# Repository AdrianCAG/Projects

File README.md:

# Projects Collection

This folder contains a collection of programs and code for you to explore, learn from, and experiment with. If you're curious and want to learn, feel free to dive in and use anything in this folder.

## License

All contents in this folder are provided under the MIT License. You are free to use, copy, modify, and distribute the code as long as you include the original copyright and license notice.

See the [MIT License](LICENSE) file for full details.

---

Happy learning and coding!

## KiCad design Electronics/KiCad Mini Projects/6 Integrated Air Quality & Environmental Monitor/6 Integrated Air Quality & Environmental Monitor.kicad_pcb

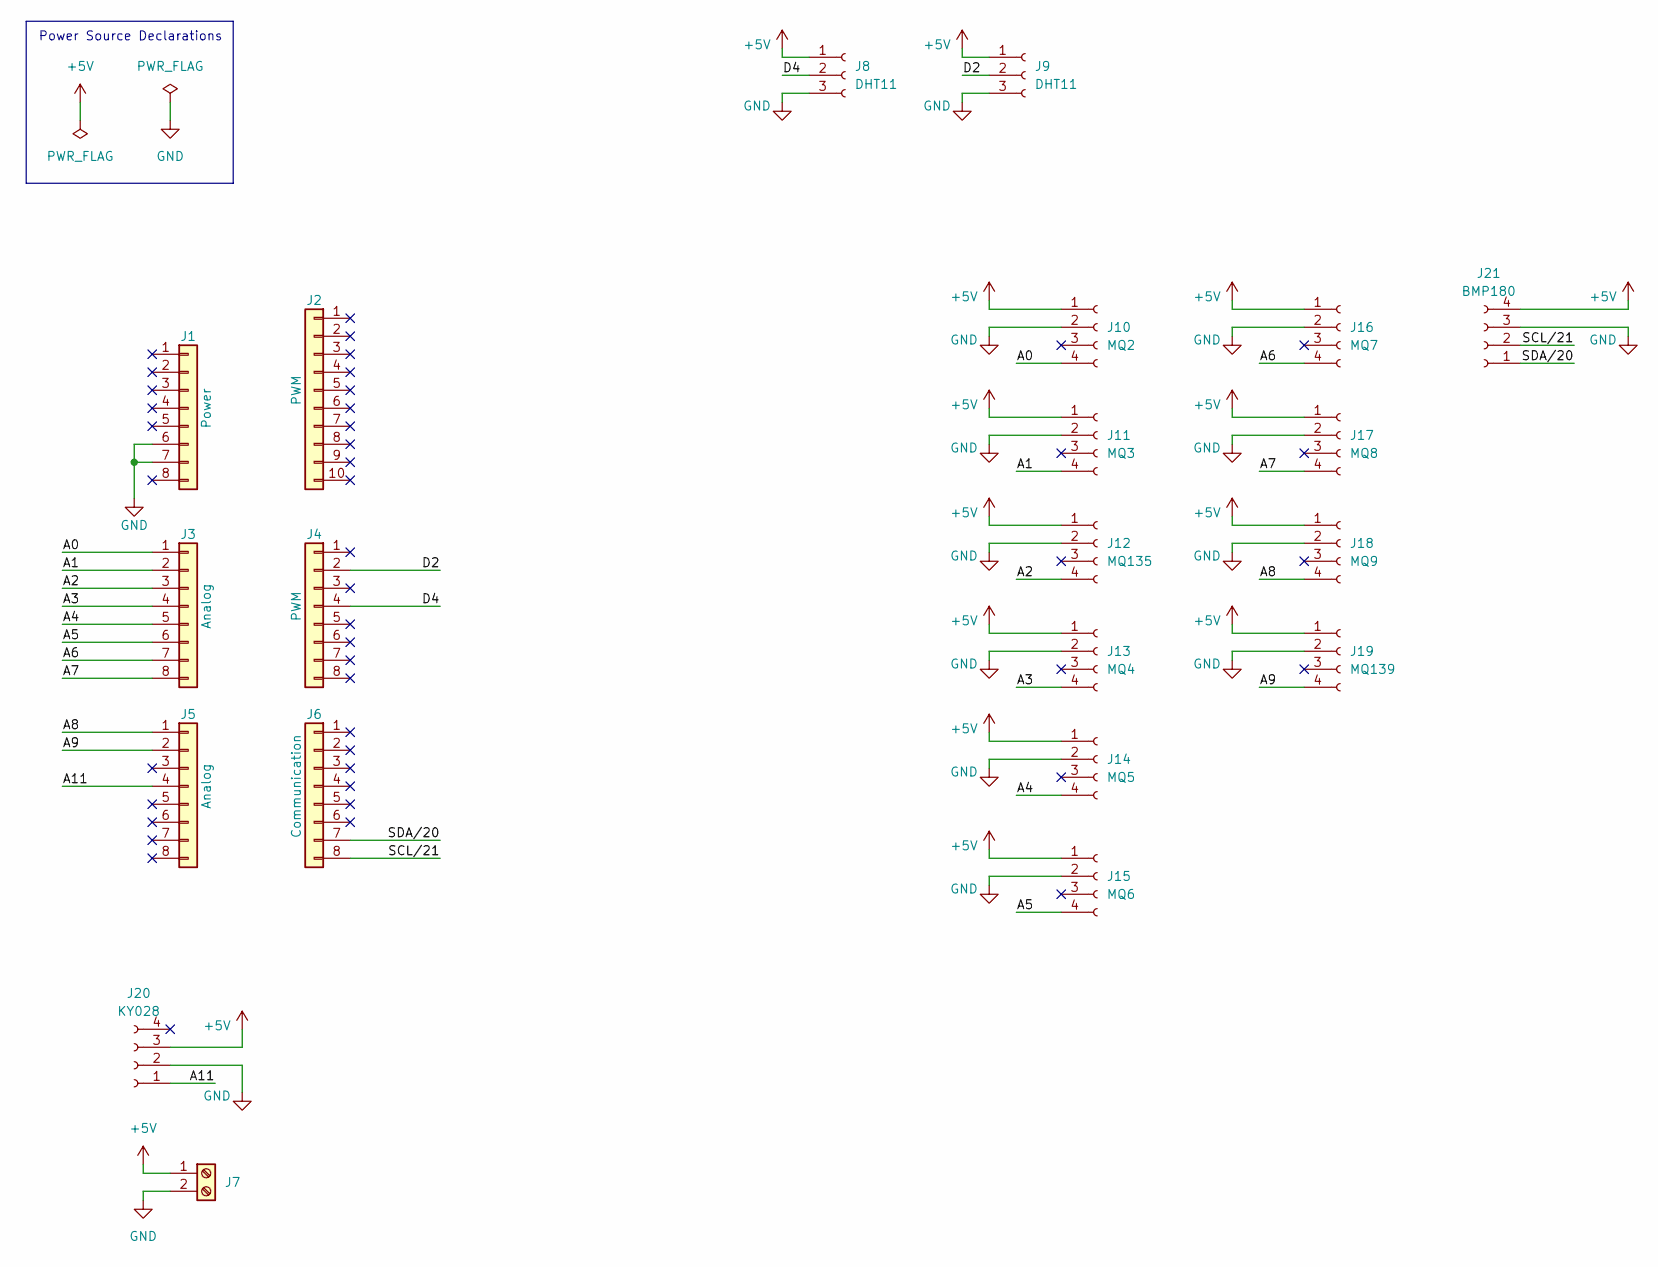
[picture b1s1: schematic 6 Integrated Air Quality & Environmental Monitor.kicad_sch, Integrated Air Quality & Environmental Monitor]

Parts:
J1: Power; PinSocket_1x08_P2.54mm_Vertical
J2: PWM; PinSocket_1x10_P2.54mm_Vertical
J3, J5: Analog; PinSocket_1x08_P2.54mm_Vertical
J4: PWM; PinSocket_1x08_P2.54mm_Vertical
J6: Communication; PinSocket_1x08_P2.54mm_Vertical
J7: Screw_Terminal_01x02; TerminalBlock_Phoenix_MKDS-1-2-3.81_1x02_P3.81mm_Horizontal
J8, J9: DHT11; PinSocket_1x03_P2.54mm_Vertical
J10: MQ2; MQ_Module_Vertical; Parts 2.54mm female header socket
J11: MQ3; MQ_Module_Vertical; Parts 2.54mm female header socket
J12: MQ135; MQ_Module_Vertical; Parts 2.54mm female header socket
J13: MQ4; PinSocket_1x04_P2.54mm_Vertical; Parts 2.54mm female header socket
J14: MQ5; PinSocket_1x04_P2.54mm_Vertical; Parts 2.54mm female header socket
J15: MQ6; MQ_Module_Vertical; Parts 2.54mm female header socket
J16: MQ7; MQ_Module_Vertical; Parts 2.54mm female header socket
J17: MQ8; MQ_Module_Vertical; Parts 2.54mm female header socket
J18: MQ9; PinSocket_1x04_P2.54mm_Vertical; Parts 2.54mm female header socket
J19: MQ139; PinHeader_1x04_P2.54mm_Vertical; Parts 2.54mm female header socket
J20: KY028; PinSocket_1x04_P2.54mm_Vertical; Parts 2.54mm female header socket
J21: BMP180; PinSocket_1x04_P2.54mm_Vertical; Parts 2.54mm female header socket

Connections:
+5V: J7.1, J8.1, J9.1, J10.1, J11.1, J12.1, J13.1, J14.1, J15.1, J16.1, J17.1, J18.1, J19.1, J20.3, J21.4
/A0: J3.1, J10.4
/A1: J3.2, J11.4
/A2: J3.3, J12.4
/A3: J3.4, J13.4
/A4: J3.5, J14.4
/A5: J3.6, J15.4
/A6: J3.7, J16.4
/A7: J3.8, J17.4
/A8: J5.1, J18.4
/A9: J5.2, J19.4
/A11: J5.4, J20.1
/D2: J4.2, J9.2
/D4: J4.4, J8.2
/SCL/21: J6.8, J21.2
/SDA/20: J6.7, J21.1
GND: J1.6, J1.7, J7.2, J8.3, J9.3, J10.2, J11.2, J12.2, J13.2, J14.2, J15.2, J16.2, J17.2, J18.2, J19.2, J20.2, J21.3

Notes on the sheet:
Power Source Declarations

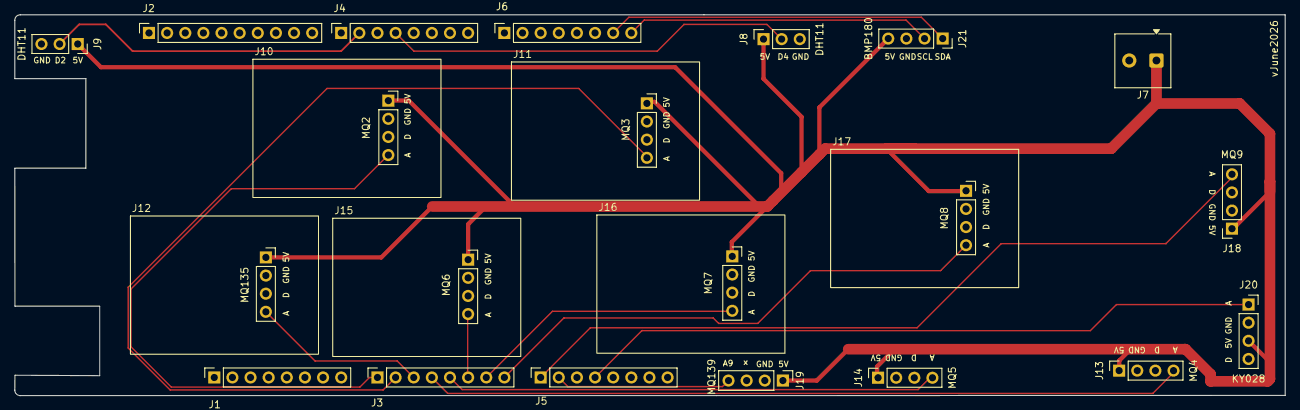
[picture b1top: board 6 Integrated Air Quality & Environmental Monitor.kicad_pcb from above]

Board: 2 copper layers, 178.0 x 53.3 mm, 21 parts (0 on the bottom side), 17 nets.

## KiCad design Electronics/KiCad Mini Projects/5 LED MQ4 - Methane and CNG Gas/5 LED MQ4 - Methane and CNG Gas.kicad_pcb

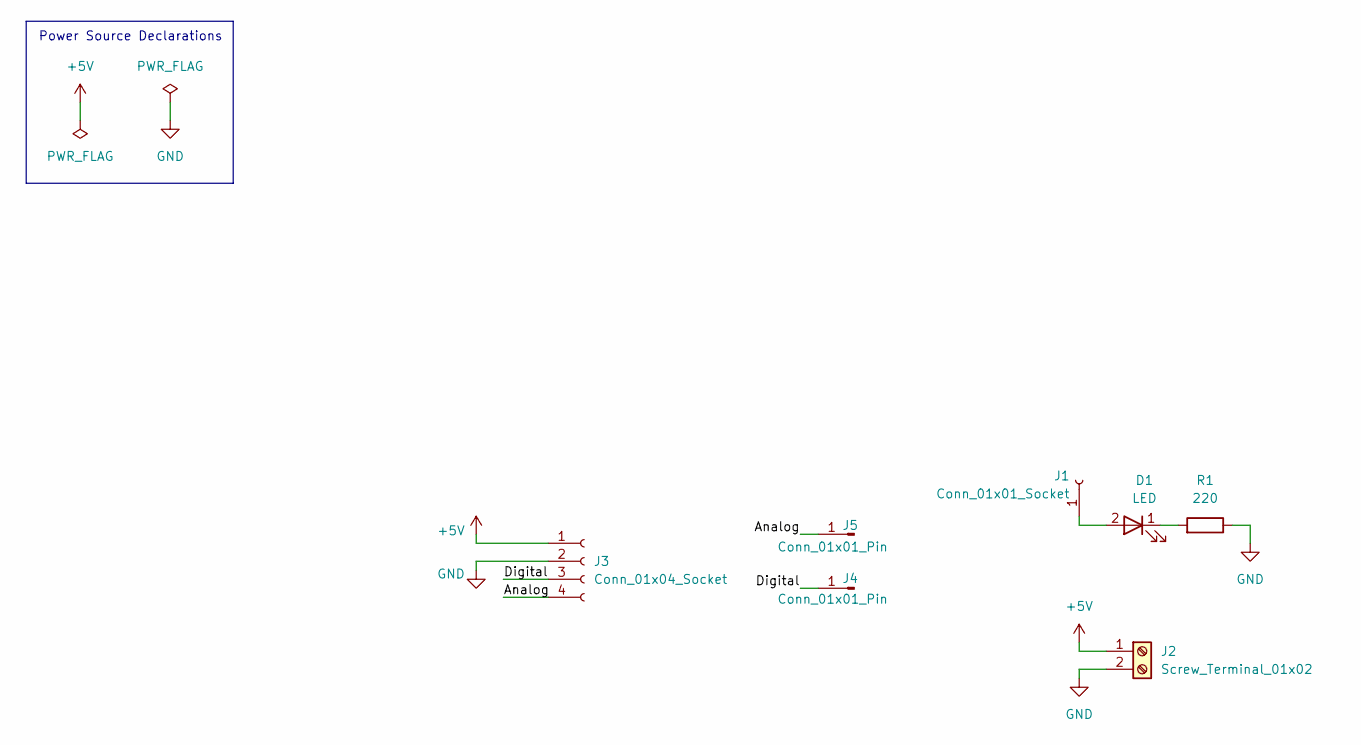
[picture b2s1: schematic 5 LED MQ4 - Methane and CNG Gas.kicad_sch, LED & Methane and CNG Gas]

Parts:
D1: LED; LED_D5.0mm; Parts 5mm LED
J1: Conn_01x01_Socket; PinSocket_1x01_P2.54mm_Vertical; Parts 2.54mm female header socket
J2: Screw_Terminal_01x02; TerminalBlock_Phoenix_MKDS-1-2-3.81_1x02_P3.81mm_Horizontal; Parts KF128 3.81mm 2P
J3: Conn_01x04_Socket; PinSocket_1x04_P2.54mm_Vertical; Parts 2.54mm female header socket
J4, J5: Conn_01x01_Pin; PinHeader_1x01_P2.54mm_Vertical; Parts 2.54mm pin header
R1: 220; R_1206_3216Metric_Pad1.30x1.75mm_HandSolder; Parts 1206 SMD resistor 220 ohm

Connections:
+5V: J2.1, J3.1
/Analog: J3.4, J5.1 (Pin_1_1)
/Digital: J3.3, J4.1 (Pin_1_1)
GND: J2.2, J3.2, R1.1
unnamed: D1.2 (A), J1.1 (Pin_1_1)
unnamed: D1.1 (K), R1.2

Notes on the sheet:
Power Source Declarations

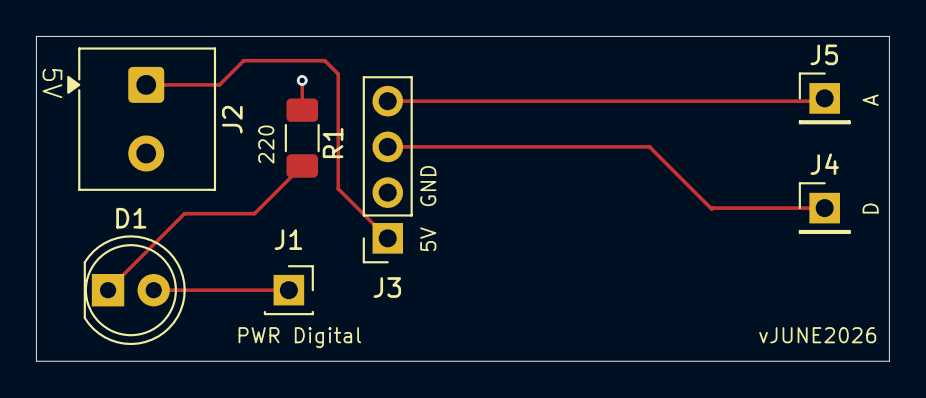
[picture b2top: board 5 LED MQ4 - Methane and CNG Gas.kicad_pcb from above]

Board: 2 copper layers, 47.4 x 18.0 mm, 7 parts (0 on the bottom side), 6 nets.

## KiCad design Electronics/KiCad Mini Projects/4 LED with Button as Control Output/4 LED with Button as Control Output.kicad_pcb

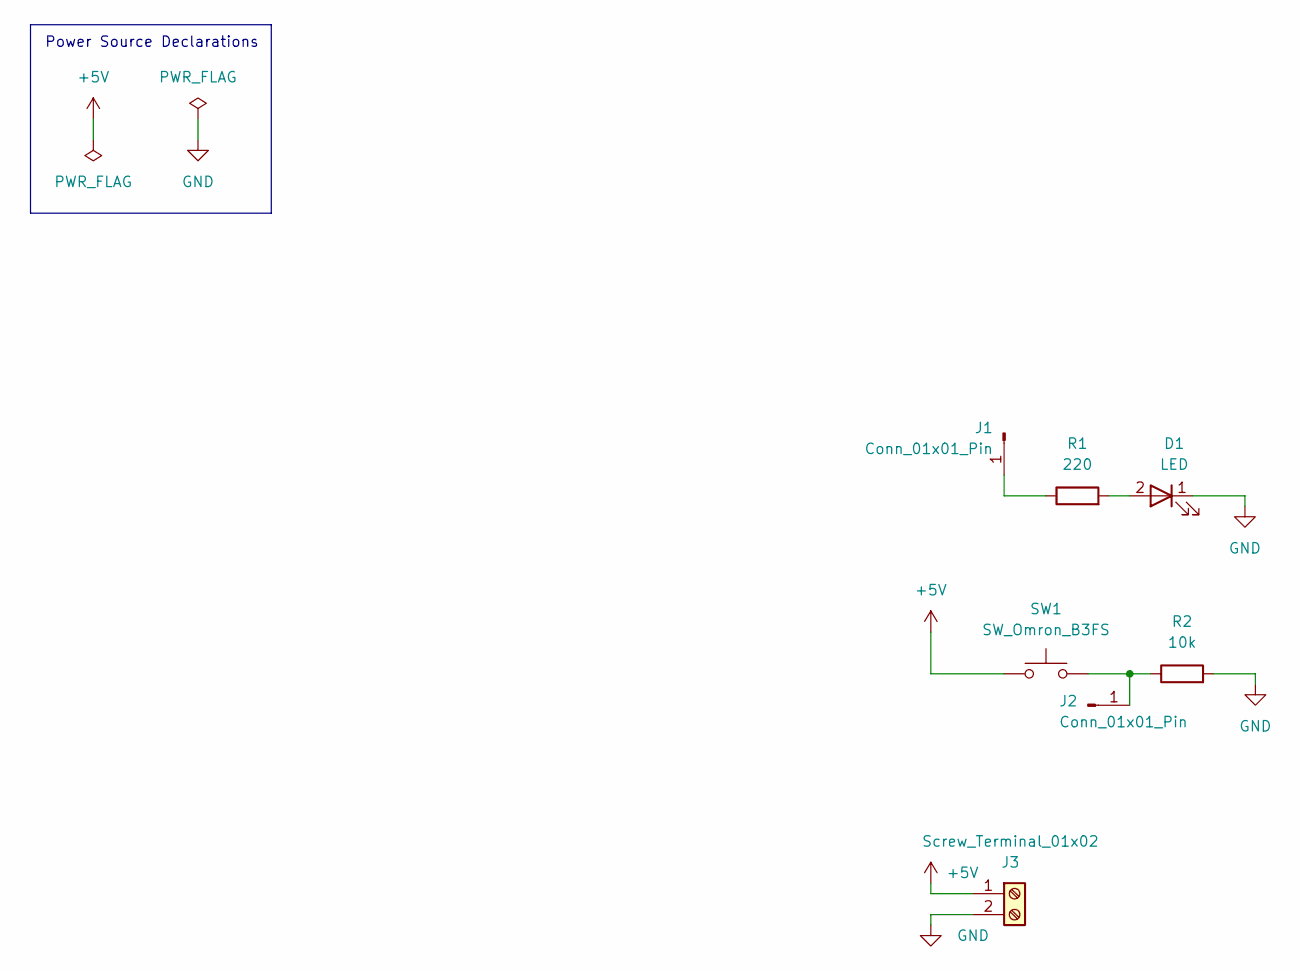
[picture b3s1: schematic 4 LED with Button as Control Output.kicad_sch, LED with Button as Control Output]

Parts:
D1: LED; LED_D5.0mm; Parts 5mm LED
J1, J2: Conn_01x01_Pin; PinHeader_1x01_P2.54mm_Vertical; Parts 2.54mm pin header
J3: Screw_Terminal_01x02; TerminalBlock_Phoenix_MKDS-1-2-3.81_1x02_P3.81mm_Horizontal; Parts KF128 3.81mm 2P
R1: 220; R_1206_3216Metric_Pad1.30x1.75mm_HandSolder; Parts 1206 SMD resistor 220 ohm
R2: 10k; R_1206_3216Metric_Pad1.30x1.75mm_HandSolder; Parts 1206 SMD resistor 10k ohm
SW1: SW_Omron_B3FS; SW_PUSH_6mm; Parts 6x6x5mm tactile switch

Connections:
+5V: J3.1, SW1.1
GND: D1.1 (K), J3.2, R2.2
unnamed: D1.2 (A), R1.2
unnamed: J1.1 (Pin_1_1), R1.1
unnamed: J2.1 (Pin_1_1), R2.1, SW1.2

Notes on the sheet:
Power Source Declarations

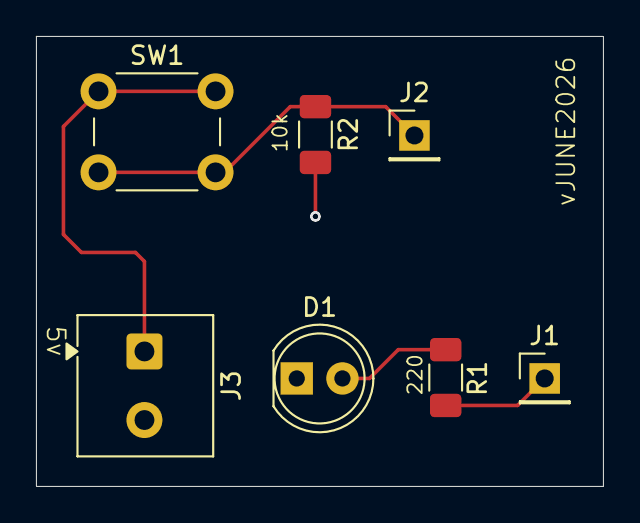
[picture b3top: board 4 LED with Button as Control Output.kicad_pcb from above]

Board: 2 copper layers, 31.5 x 25.0 mm, 7 parts (0 on the bottom side), 5 nets.

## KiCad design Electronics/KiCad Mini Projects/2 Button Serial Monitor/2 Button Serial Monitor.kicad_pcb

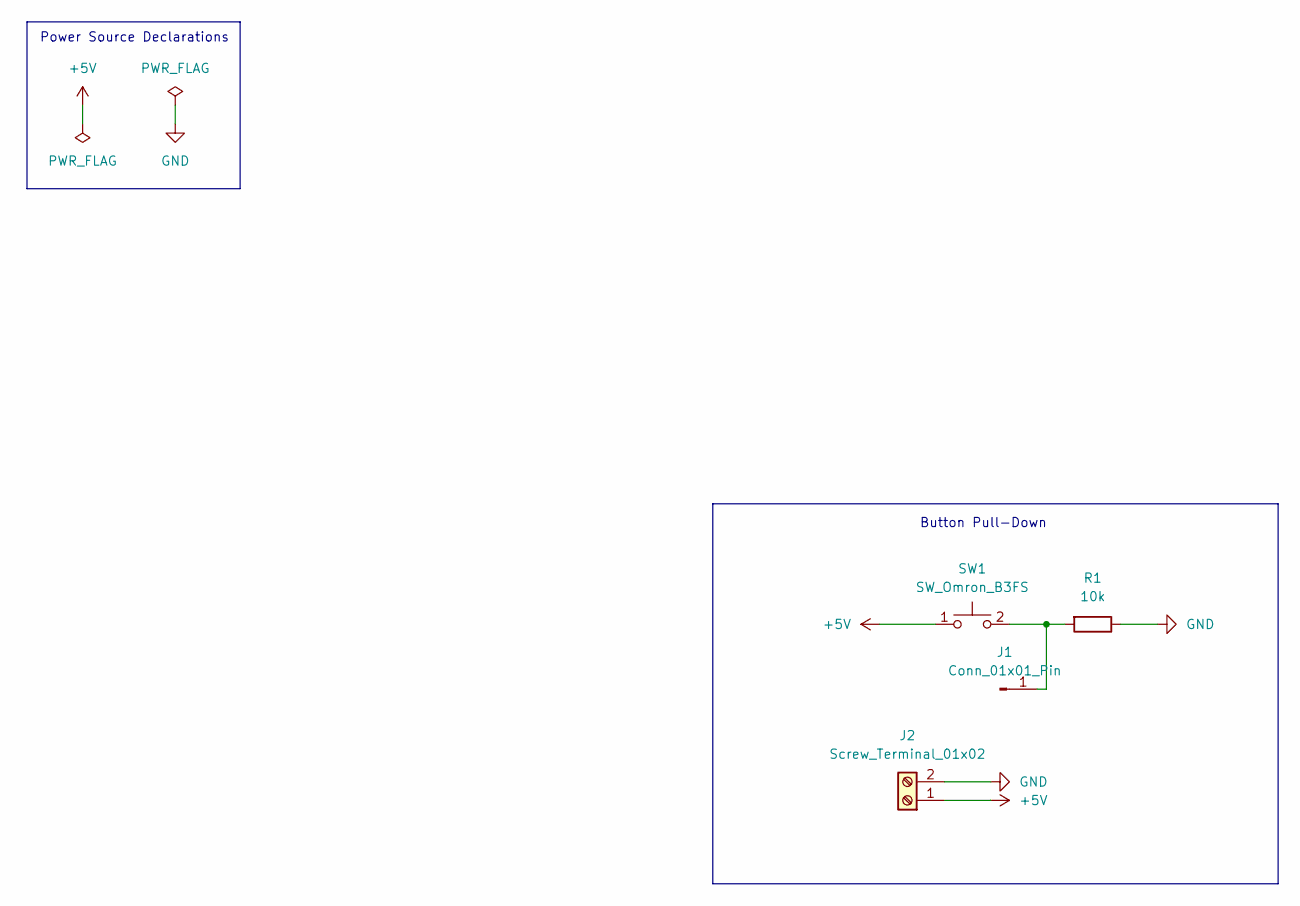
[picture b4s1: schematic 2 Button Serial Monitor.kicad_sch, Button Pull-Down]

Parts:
J1: Conn_01x01_Pin; PinHeader_1x01_P2.54mm_Vertical; Part 2.54mm pin header
J2: Screw_Terminal_01x02; TerminalBlock_Phoenix_MKDS-1-2-3.81_1x02_P3.81mm_Horizontal; Part KF128 3.81mm 2P
R1: 10k; R_1206_3216Metric_Pad1.30x1.75mm_HandSolder; Part 1206 SMD resistor 10k ohm
SW1: SW_Omron_B3FS; SW_PUSH_6mm; Part 6x6x5mm tactile switch

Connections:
+5V: J2.1, SW1.1
GND: J2.2, R1.1
unnamed: J1.1 (Pin_1_1), R1.2, SW1.2

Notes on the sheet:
Power Source Declarations
Button Pull-Down

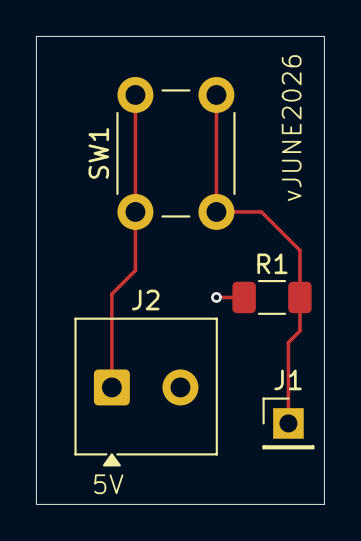
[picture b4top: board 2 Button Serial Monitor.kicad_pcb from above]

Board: 2 copper layers, 16.0 x 26.0 mm, 4 parts (0 on the bottom side), 3 nets.

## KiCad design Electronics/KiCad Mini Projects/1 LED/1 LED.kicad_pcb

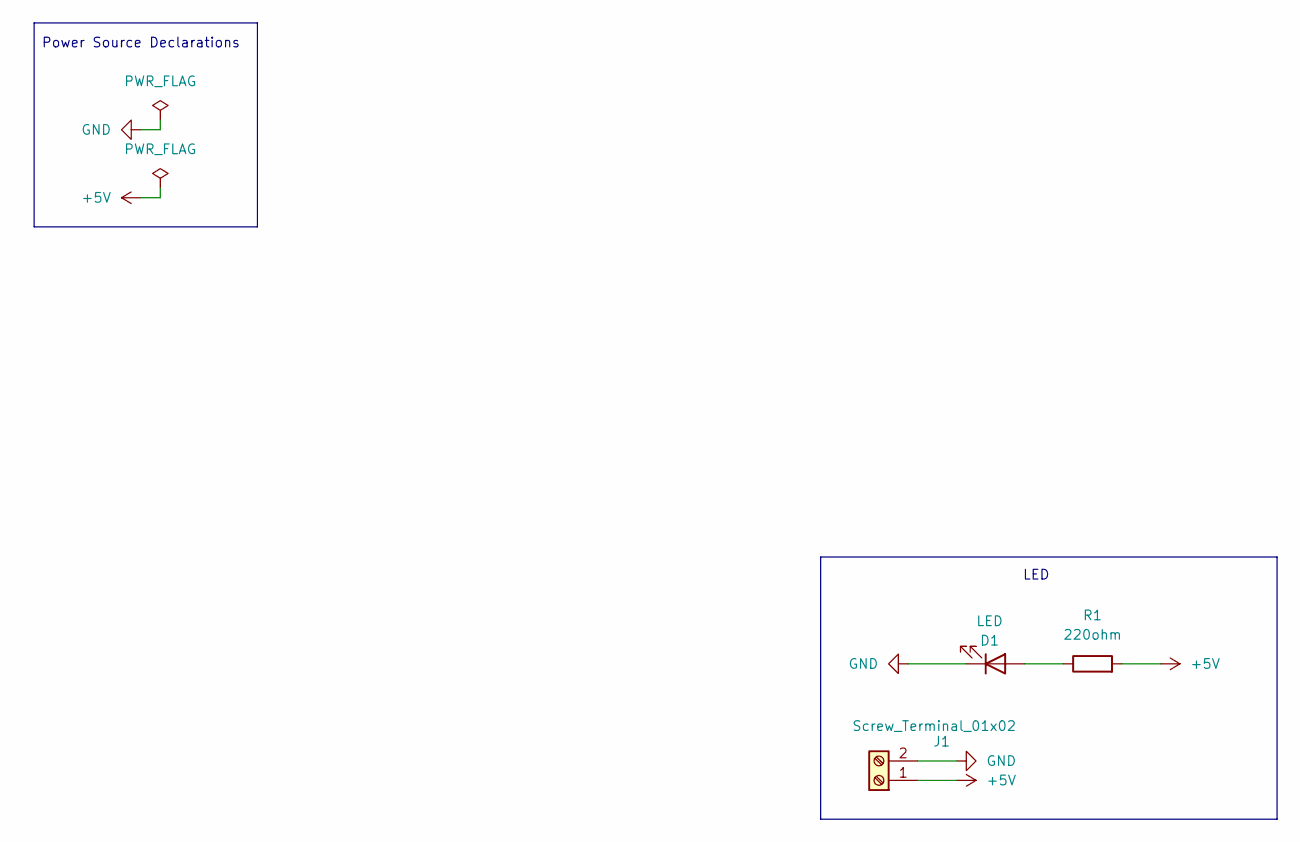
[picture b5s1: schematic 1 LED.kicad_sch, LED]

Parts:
D1: LED; LED_D5.0mm; Part 5mm LED
J1: Screw_Terminal_01x02; TerminalBlock_Phoenix_MKDS-1-2-3.81_1x02_P3.81mm_Horizontal; Part KF128 3.81mm 2P
R1: 220ohm; R_1206_3216Metric_Pad1.30x1.75mm_HandSolder; Part 1206 SMD resistor 220 ohm

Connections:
+5V: J1.1, R1.2
GND: D1.1 (K), J1.2
unnamed: D1.2 (A), R1.1

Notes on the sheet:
LED
Power Source Declarations

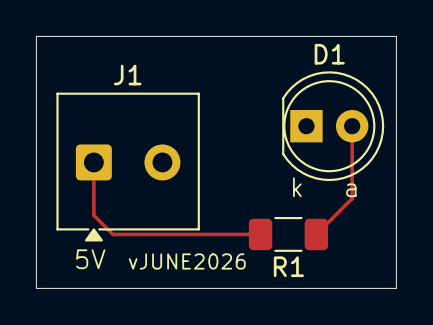
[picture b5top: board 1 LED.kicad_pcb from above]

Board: 2 copper layers, 20.0 x 14.0 mm, 3 parts (0 on the bottom side), 3 nets.

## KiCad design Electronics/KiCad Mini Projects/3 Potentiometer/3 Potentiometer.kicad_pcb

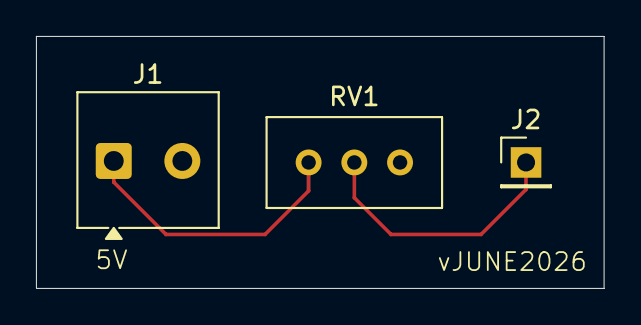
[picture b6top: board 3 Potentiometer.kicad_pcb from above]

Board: 2 copper layers, 31.5 x 14.0 mm, 3 parts (0 on the bottom side), 3 nets.

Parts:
J1: Screw_Terminal_01x02; TerminalBlock_Phoenix_MKDS-1-2-3.81_1x02_P3.81mm_Horizontal
J2: Conn_01x01_Pin; PinHeader_1x01_P2.54mm_Vertical
RV1: R_Potentiometer_Trim; Potentiometer_Bourns_3296W_Vertical

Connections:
+5V: J1.1, RV1.3
GND: J1.2, RV1.1
unnamed: J2.1 (Pin_1_1), RV1.2

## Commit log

2024-06-12 ComputAverageProject
2024-06-12 Compute Average Project
2024-06-12 Addition Project
2024-06-14 Addition Project files
2024-06-14 Breakout Project files
2024-07-10 Space Invaders Project Files
2024-08-18 Made Up Programming Language Project files
2024-08-18 Rename LICENSE.txt to LICENSE
2024-09-07 Number to Text Project files
2024-09-15 Arduino Mini Projects files
2024-09-29 Dynamic Dispatch Project files
2024-10-21 Cpp Dynamic Dispatch Project files
2025-01-12 Double Dispatch vs Pattern Matching Project files
2025-04-20 Create LICENSE
2025-04-20 Medical Instruments Project files
2025-04-23 Calendar files
2025-05-08 Learning OOP Project files
2025-05-11 Arduino Sensor Graph Display files
2025-05-24 Simple Drawing Player files
2025-05-24 Data Visualization files
2025-05-24 Exo-Verse files
2025-09-22 Arduino Mini Projects fies
2025-09-22 Data - Sensor Logs CSV
2026-06-08 KiCad Mini Projects files
